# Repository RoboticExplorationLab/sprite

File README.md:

[hardware](https://github.com/maholli/sprite/tree/master/hardware): KiCad PCB files and bill of materials. Assembling a sprite? Check out [https://roboticexplorationlab.github.io/sprite/](https://roboticexplorationlab.github.io/sprite/) for an interactive BOM!

[firmware](https://github.com/maholli/sprite/tree/master/firmware): pre-built circuitpython bootloader.bin and firmware.uf2 (and the files to build it yourself)

[software](https://github.com/maholli/sprite/tree/master/software): circuitpython scripts and libraries working on the sprite

<br>
<br>
<br>

----

### 💡 Lots of applicable information also located on the [PyCubed.org quickstart page](https://www.notion.so/maholli/Hands-On-Quick-Start-d220f0ec88eb41c08ee855ff4f46d737).

## Demos

Put all the files located in [/software/](/software/) on to the sprite and start the serial console (as described above). After pressing <kbd>Ctrl</kbd>+<kbd>C</kbd> to halt the sprite, press any key to enter the REPL, then type

```
import NAMEOFFILE
```

and press enter to execute the example. For example, it we wanted to run blink.py, it would be...

```
import blink
```

1. blink.py - will blink the green LED. 
2. i2c_IMU.py - samples all available sensors on the IMU and prints the results
3. cursor.py - uses the X,Y data from the IMU accelerometer and moves the computer cursor accordingly
4. cpc_test.py - example transmit message for the CC1101 radio

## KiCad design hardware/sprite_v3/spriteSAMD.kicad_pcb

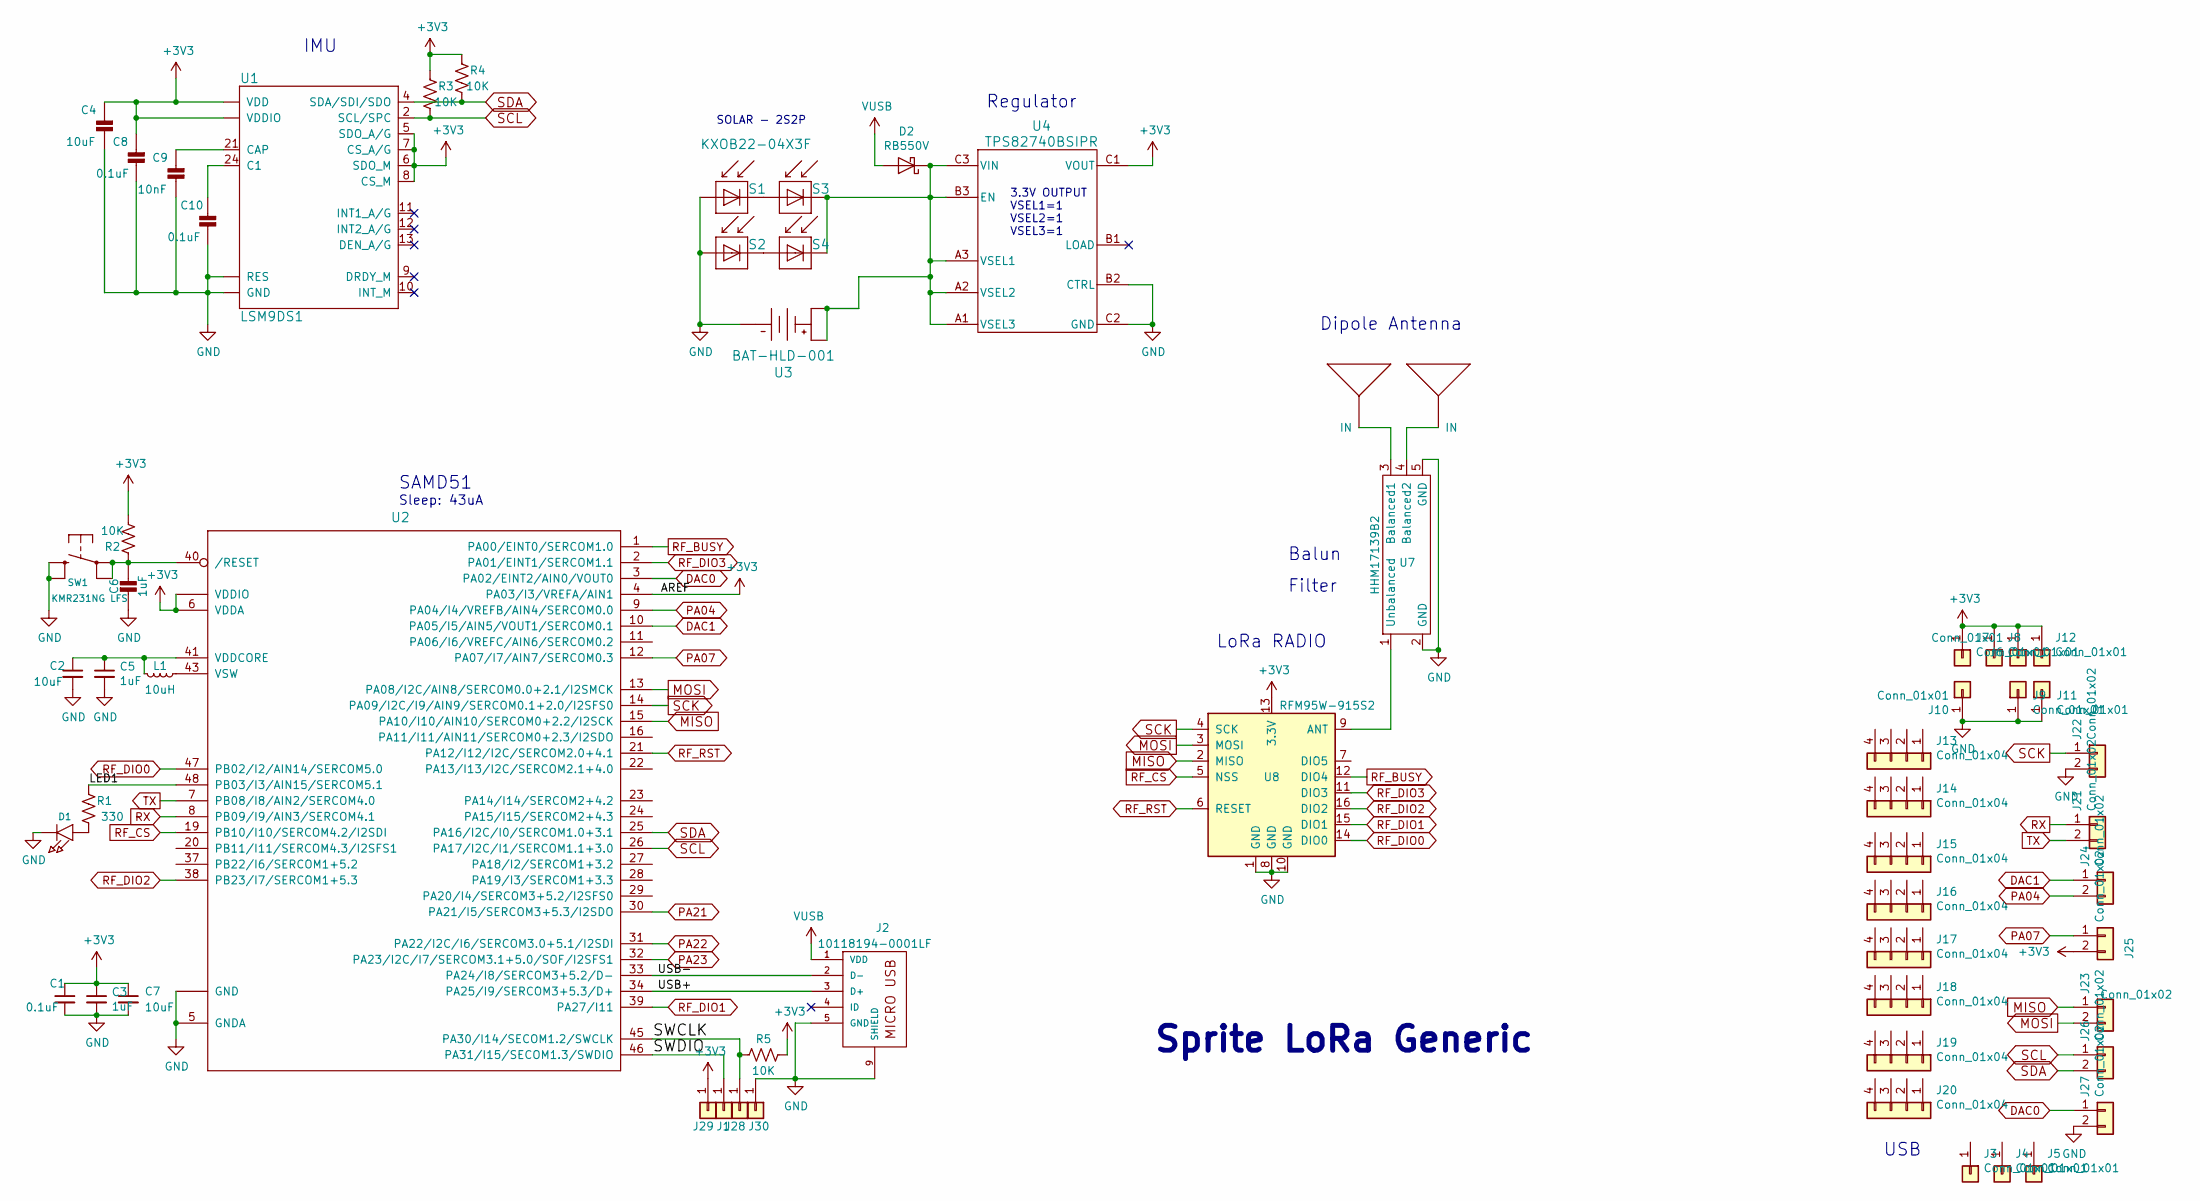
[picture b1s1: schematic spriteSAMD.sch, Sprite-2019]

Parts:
ANT1, ANT2: ANTENNA
C1, C8, C10: 0.1uF; C_0402_1005Metric
C2, C4, C7: 10uF; C_0402_1005Metric
C3, C5, C6: 1uF; C_0402_1005Metric
C9: 10nF; C_0402_1005Metric
D1: GREEN; LED_0603_1608Metric
D2: RB550V; D_SOD-323
J1, J28, J29, J30: Conn_01x01; castellated_small_1side
J2: 10118194-0001LF
J3, J4, J5, J6, J7, J8, J9, J10, J11, J12: Conn_01x01; PinHeader_CUSTOM2
J13, J14, J15, J16, J17, J18, J19, J20: Conn_01x04; PinHeader_CUSTOM
J21, J22, J23, J24, J25, J26, J27: Conn_01x02; PinHeader_CUSTOM3
L1: 10uH; L_0805_2012Metric
R1: 330; R_0402_1005Metric
R2, R3, R4, R5: 10K; R_0402_1005Metric
S1, S2, S3, S4: KXOB22-04X3F; KXOB22-12X1F
SW1: KMR231NG LFS; BTN_KMR2_4.6X2.8
U1: LSM9DS1; LGA24-8X4
U2: ATSAMD51G_TQFN48; QFN50P700X700X90-49N-D
U3: BAT-HLD-001
U4: TPS82740BSIPR; TPS82740ASIPR
U7: HHM17139B2; balun0603
U8: RFM95W-915S2; HOPERF_RFM9XW_SMD

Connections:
+3V3: C1.1, C3.1, C4.2, C7.1, C8.2, J6.1, J7.1, J8.1, J12.1, J25.2, J29.1, R2.2, R3.1, R4.1, R5.1, U1.1 (VDDIO), U1.3 (VDDIO), U1.5 (SDO_A/G), U1.6 (SDO_M), U1.7 (CS_A/G), U1.8 (CS_M), U1.22 (VDD), U1.23 (VDD), U2.4 (PA03/I3/VREFA/AIN1), U2.6 (VDDA), U2.17 (VDDIO), U2.36 (VDDIO), U2.44 (VDDIO), U4.C1 (VOUT), U8.13 (3.3V)
/LED1: R1.2, U2.48 (PB03/I3/AIN15/SERCOM5.1)
/SWCLK: J28.1, R5.2, U2.45 (PA30/I14/SECOM1.2/SWCLK)
/SWDIO: J1.1, U2.46 (PA31/I15/SECOM1.3/SWDIO)
/USB+: J2.3 (D+), U2.34 (PA25/I9/SERCOM3+5.3/D+)
/USB-: J2.2 (D-), U2.33 (PA24/I8/SERCOM3+5.2/D-)
DAC0: J27.1, U2.3 (PA02/EINT2/AIN0/VOUT0)
DAC1: J24.1, U2.10 (PA05/I5/AIN5/VOUT1/SERCOM0.1)
GND: C1.2, C2.2, C3.2, C4.1, C5.2, C6.1, C7.2, C8.1, C9.1, C10.1, D1.2, J2.5 (GND), J2.8, J2.9 (SHIELD), J9.1, J10.1, J11.1, J22.2, J27.2, J30.1, S1.2, S2.2, SW1.B (S), SW1.B' (S1), U1.14 (RES), U1.15 (RES), U1.16 (RES), U1.17 (RES), U1.18 (RES), U1.19 (GND), U1.20 (GND), U2.5 (GNDA), U2.18 (GND), U2.35 (GND), U2.42 (GND), U2.49, U3.2, U4.B2 (CTRL), U4.C2 (GND), U7.2 (GND), U7.5 (GND), U7.6 (NC), U8.1 (GND), U8.8 (GND), U8.10 (GND)
MISO: J23.1, U2.15 (PA10/I10/AIN10/SERCOM0+2.2/I2SCK), U8.2 (MISO)
MOSI: J23.2, U2.13 (PA08/I2C/AIN8/SERCOM0.0+2.1/I2SMCK), U8.3 (MOSI)
unnamed: ANT1.IN1, ANT1.IN2, ANT1.IN3, U7.3 (Balanced1)
unnamed: ANT2.IN1, ANT2.IN2, ANT2.IN3, U7.4 (Balanced2)
unnamed: C2.1, C5.1, L1.2, U2.41 (VDDCORE)
unnamed: C6.2, R2.1, SW1.A, SW1.A' (P1), U2.40 (/RESET)
unnamed: C9.2, U1.21 (CAP)
unnamed: C10.2, U1.24 (C1)
unnamed: D1.1, R1.1
unnamed: D2.1 (K), S3.1, S4.1, U3.1, U3.3, U4.A1 (VSEL3), U4.A2 (VSEL2), U4.A3 (VSEL1), U4.B3 (EN), U4.C3 (VIN)
unnamed: L1.1, U2.43 (VSW)
unnamed: S1.1, S3.2
unnamed: S2.1, S4.2
unnamed: U7.1 (Unbalanced), U8.9 (ANT)
PA04: J24.2, U2.9 (PA04/I4/VREFB/AIN4/SERCOM0.0)
PA07: J25.1, U2.12 (PA07/I7/AIN7/SERCOM0.3)
PA21: U2.30 (PA21/I5/SERCOM3+5.3/I2SDO)
PA22: U2.31 (PA22/I2C/I6/SERCOM3.0+5.1/I2SDI)
PA23: U2.32 (PA23/I2C/I7/SERCOM3.1+5.0/SOF/I2SFS1)
RF_BUSY: U2.1 (PA00/EINT0/SERCOM1.0), U8.12 (DIO4)
RF_CS: U2.19 (PB10/I10/SERCOM4.2/I2SDI), U8.5 (NSS)
RF_DIO0: U2.47 (PB02/I2/AIN14/SERCOM5.0), U8.14 (DIO0)
RF_DIO1: U2.39 (PA27/I11), U8.15 (DIO1)
RF_DIO2: U2.38 (PB23/I7/SERCOM1+5.3), U8.16 (DIO2)
RF_DIO3: U2.2 (PA01/EINT1/SERCOM1.1), U8.11 (DIO3)
RF_RST: U2.21 (PA12/I12/I2C/SERCOM2.0+4.1), U8.6 (RESET)
RX: J21.1, U2.8 (PB09/I9/AIN3/SERCOM4.1)
SCK: J22.1, U2.14 (PA09/I2C/I9/AIN9/SERCOM0.1+2.0/I2SFS0), U8.4 (SCK)
SCL: J26.1, R3.2, U1.2 (SCL/SPC), U2.26 (PA17/I2C/I1/SERCOM1.1+3.0)
SDA: J26.2, R4.2, U1.4 (SDA/SDI/SDO), U2.25 (PA16/I2C/I0/SERCOM1.0+3.1)
TX: J21.2, U2.7 (PB08/I8/AIN2/SERCOM4.0)
VUSB: D2.2 (A), J2.1 (VDD)

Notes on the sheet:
Regulator
USB
IMU
3.3V OUTPUT VSEL1=1 VSEL2=1 VSEL3=1
SOLAR - 2S2P
SAMD51
LoRa RADIO
Sleep: 43uA
Balun
Filter
Dipole Antenna
Sprite LoRa Generic

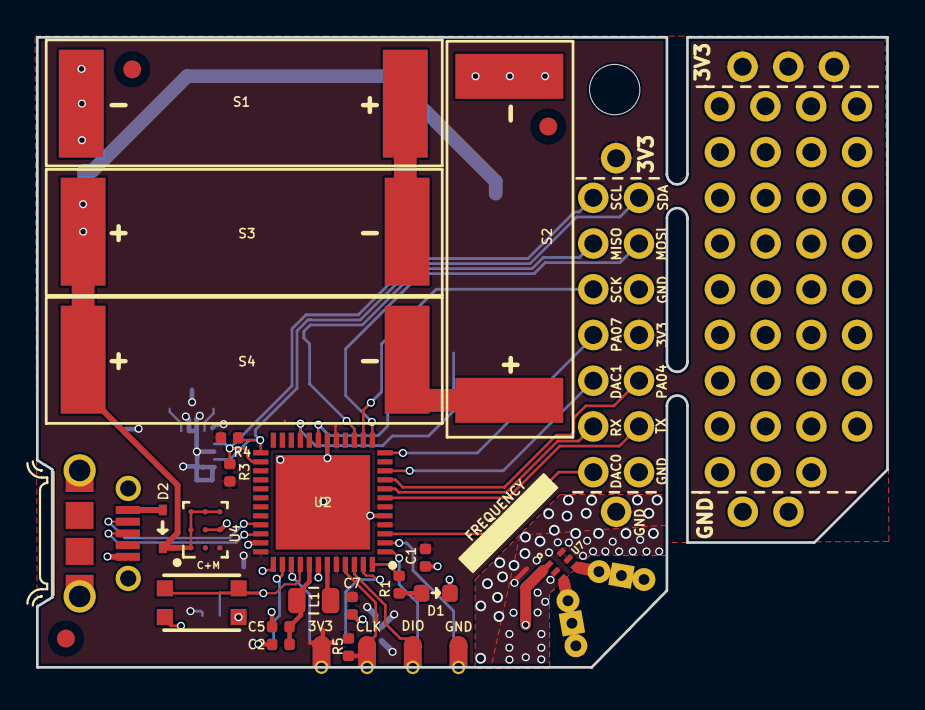
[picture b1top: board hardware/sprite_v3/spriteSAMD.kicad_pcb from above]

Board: 2 copper layers, 47.2 x 35.0 mm, 62 parts (0 on the bottom side), 38 nets.

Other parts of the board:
@HOLE0: (no value)

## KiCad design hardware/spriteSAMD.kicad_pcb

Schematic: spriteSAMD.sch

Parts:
ANT-N1: ANTENNA
ANT-P1: ANTENNA
C1, C30, C34: 10uF; C_0402_1005Metric
C2, C3, C4, C6, C8, C9, C10, C32: 0.1uF; C_0402_1005Metric
C5, C18, C20: 10nF; C_0402_1005Metric
C7, C29, C31, C33: 1uF; C_0402_1005Metric
C16, C17, C19: 220pF; C_0402_1005Metric
C21, C22: 100nF; C_0402_1005Metric
C25: 27pF; C_0402_1005Metric
D1: MBR120; D_SOD-123
D3: GREEN LED; LED_0603_1608Metric
J1: 10118194-0001LF
J2, J4, J5, J6, J7, J8, J9, J10, J11, J12: Conn_01x01; PinHeader_CUSTOM2
J3: Conn_01x04; PinHeader_1x04_P2.54mm_Vertical
J13, J14, J15, J16, J17, J18, J19, J20: Conn_01x04; PinHeader_CUSTOM
J21, J22, J23, J24, J25, J26, J27: Conn_01x02; PinHeader_CUSTOM3
JP1: SolderJumper_3_Bridged12; Jumper3_Small
L1: 10uH; L_0805_2012Metric
R6: 330; R_0402_1005Metric
R7, R8, R9, R13: 10K; R_0402_1005Metric
R11: 56K; R_0402_1005Metric
S1, S2, S3, S5: KXOB22-04X3F; KXOB22-12X1F
SW2: KMR231NG LFS; BTN_KMR2_4.6X2.8
U1: BAT-HLD-001
U2: CC1101RGPR; CC1101_RGP_20; MPN CC1101RGPR; Digi-Key_PN 296-35718-1-ND
U3: LSM9DS1; LGA24-8X4
U4: TPS82740ASIP; TPS82740ASIPR
U6: ATSAMD51G_TQFN48; QFN50P700X700X90-49N-D
U7: OVM9724; OVM9724b
U8, U9: DS90LV012ATMFX_NOPB; DS90
X1: 26.000; TXCO_2.5x2

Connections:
+2V1: C1.2, C2.1, C3.1, C4.2, C16.2, C17.1, C18.1, C19.1, C20.1, C22.2, C31.2, C32.1, C33.1, C34.1, J3.4, J6.1, J9.1, J11.1, R7.1, R8.1, R9.2, R13.1, U2.4, U2.9, U2.11, U2.14, U2.15, U2.18, U3.1 (VDDIO), U3.3 (VDDIO), U3.5 (SDO_A/G), U3.6 (SDO_M), U3.7 (CS_A/G), U3.8 (CS_M), U3.22 (VDD), U3.23 (VDD), U4.C1 (VOUT), U6.6 (VDDA), U6.17 (VDDIO), U6.36 (VDDIO), U6.44 (VDDIO), U7.C2 (DOVDD), U7.C7 (DVDD), U7.D6 (DOVDD), U8.1 (Vdd), U9.1 (Vdd), X1.4
/AREF: C31.1, U6.4 (PA03/I3/VREFA/AIN1)
/AVDD: C8.1, U7.A2 (AVDD)
/LED1: R6.2, U6.48 (PB03/I3/AIN15/SERCOM5.1)
/SWCLK: J3.2, R13.2, U6.45 (PA30/I14/SECOM1.2/SWCLK)
/SWDIO: J3.3, U6.46 (PA31/I15/SECOM1.3/SWDIO)
/USB+: J1.3 (D+), U6.34 (PA25/I9/SERCOM3+5.3/D+)
/USB-: J1.2 (D-), U6.33 (PA24/I8/SERCOM3+5.2/D-)
/VREF1: C9.1, U7.D2 (VREF1)
/VREF2: C10.1, U7.D3 (VREF2)
DAC0: J27.1, U6.3 (PA02/EINT2/AIN0/VOUT0)
FSYNC: U6.22 (PA13/I13/I2C/SERCOM2.1+4.0), U6.24 (PA15/I15/SERCOM2+4.3), U7.C5 (GPIO0/FSIN)
MC: U6.28 (PA19/I3/SERCOM1+3.3), U9.5 (TTLout)
MD: U6.27 (PA18/I2/SERCOM1+3.2), U8.5 (TTLout)
MISO: J21.2, U2.2, U6.9 (PA04/I4/VREFB/AIN4/SERCOM0.0)
MOSI: J24.2, U2.20, U6.12 (PA07/I7/AIN7/SERCOM0.3)
unnamed: ANT-N1.IN1, ANT-N1.IN2, ANT-N1.IN3, U2.13
unnamed: ANT-P1.IN1, ANT-P1.IN2, ANT-P1.IN3, U2.12
unnamed: C5.2, U3.21 (CAP)
unnamed: C6.2, U3.24 (C1)
unnamed: C21.1, U2.5
unnamed: C25.1, U2.8
unnamed: C25.2, X1.3
unnamed: C29.2, R9.1, SW2.A, SW2.A' (P1), U6.40 (/RESET)
unnamed: C7.2, C30.2, L1.2, U6.41 (VDDCORE)
unnamed: D1.1, JP1.3, S2.1, S3.1, U1.1, U1.3, U4.A2 (VSEL2), U4.A3 (VSEL1), U4.B3 (EN), U4.C3 (VIN)
unnamed: D3.1, R6.1
unnamed: JP1.2, U4.A1 (VSEL3)
unnamed: L1.1, U6.43 (VSW)
unnamed: R11.1, U2.17
unnamed: S1.1, S2.2
unnamed: S3.2, S5.1
unnamed: U7.A5 (MDP), U8.4 (IN-)
unnamed: U7.B5 (MDN), U8.3 (IN+)
unnamed: U7.B6 (MCN), U9.4 (IN-)
unnamed: U7.C6 (MCP), U9.3 (IN+)
PA06: J24.1, U6.11 (PA06/I6/VREFC/AIN6/SERCOM0.2)
PA08: J22.1, U6.13 (PA08/I2C/AIN8/SERCOM0.0+2.1/I2SMCK)
PA09: J23.2, U6.14 (PA09/I2C/I9/AIN9/SERCOM0.1+2.0/I2SFS0)
PA10: J23.1, U6.15 (PA10/I10/AIN10/SERCOM0+2.2/I2SCK)
PA21: U6.30 (PA21/I5/SERCOM3+5.3/I2SDO)
PA22: U6.31 (PA22/I2C/I6/SERCOM3.0+5.1/I2SDI)
PA23: U6.32 (PA23/I2C/I7/SERCOM3.1+5.0/SOF/I2SFS1)
PB02: U6.47 (PB02/I2/AIN14/SERCOM5.0)
PWDWN: U6.20 (PB11/I11/SERCOM4.3/I2SFS1), U7.B1 (PWDNB)
RX: J25.1, U6.7 (PB08/I8/AIN2/SERCOM4.0)
SCK: J21.1, U2.1, U6.10 (PA05/I5/AIN5/VOUT1/SERCOM0.1)
SCL: J26.2, R7.2, U3.2 (SCL/SPC), U6.26 (PA17/I2C/I1/SERCOM1.1+3.0), U7.A4 (SCL)
SDA: J26.1, R8.2, U3.4 (SDA/SDI/SDO), U6.25 (PA16/I2C/I0/SERCOM1.0+3.1), U7.A6 (SDA)
SHDWN: U6.19 (PB10/I10/SERCOM4.2/I2SDI), U7.B2 (~SHUTDOWN)
TST: U6.16 (PA11/I11/AIN11/SERCOM0+2.3/I2SDO), U7.B3 (TM)
TX: J25.2, U6.8 (PB09/I9/AIN3/SERCOM4.1)
VCLK: U6.23 (PA14/I14/SERCOM2+4.2), U7.C3 (~VCLK)
VUSB: D1.2, J1.1 (VDD)
WAKE: U2.6, U6.2 (PA01/EINT1/SERCOM1.1)
radioCS: U2.7, U6.1 (PA00/EINT0/SERCOM1.0)

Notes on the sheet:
REGULATOR
PCCDEN1
PCCDEN2
PCCD0
PCCD1
PCCD2
PCCD3
PCCD4
PCCD5
PCCD6
PCCD7
PCCLK
USB
IMU
100ohm diff pair
I2C=0x20
2.1V OUTPUT VSEL1=1 VSEL2=1 VSEL3=0
SOLAR - 2S2P
Sprite - 2019
SAMD51

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
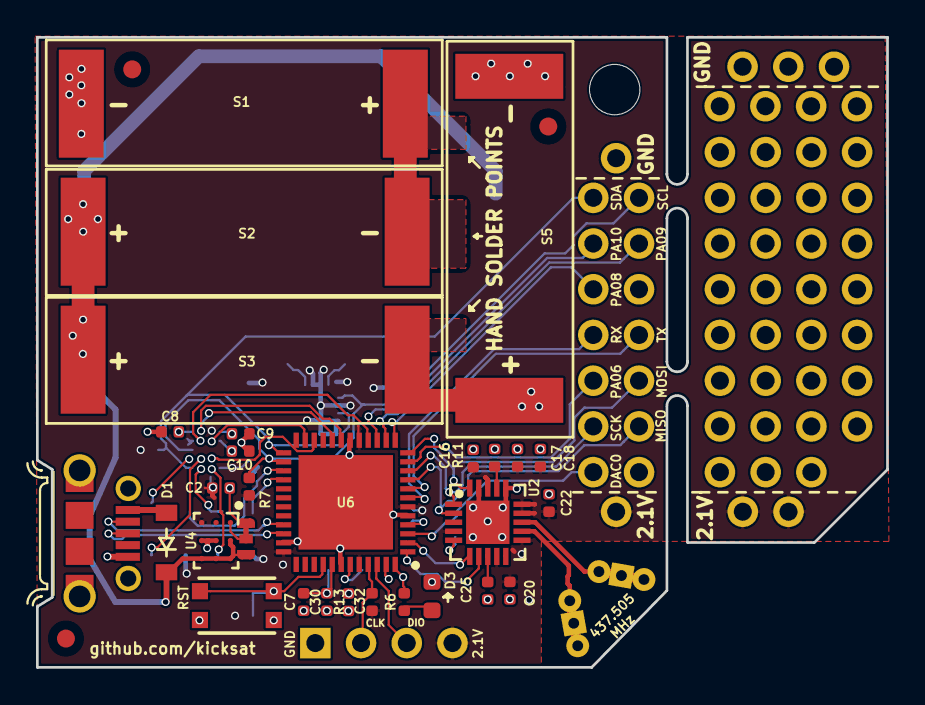
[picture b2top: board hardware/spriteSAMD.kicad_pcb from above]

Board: 2 copper layers, 47.2 x 35.0 mm, 78 parts (0 on the bottom side), 53 nets.

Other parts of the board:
@HOLE0: (no value)

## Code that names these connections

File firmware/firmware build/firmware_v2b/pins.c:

#include "shared-bindings/board/__init__.h"

#include "supervisor/shared/board_busses.h"

STATIC const mp_rom_map_elem_t board_global_dict_table[] = {
    { MP_ROM_QSTR(MP_QSTR_SCK),     MP_ROM_PTR(&pin_PA05)  },
    { MP_ROM_QSTR(MP_QSTR_MOSI),    MP_ROM_PTR(&pin_PA07)  },
    { MP_ROM_QSTR(MP_QSTR_MISO),    MP_ROM_PTR(&pin_PA04)  },

    { MP_ROM_QSTR(MP_QSTR_radioCS), MP_ROM_PTR(&pin_PA00)  },
    { MP_ROM_QSTR(MP_QSTR_WAKE),    MP_ROM_PTR(&pin_PA01)  },
	{ MP_ROM_QSTR(MP_QSTR_SHDWN),   MP_ROM_PTR(&pin_PB10)  },
    { MP_ROM_QSTR(MP_QSTR_PWDWN),   MP_ROM_PTR(&pin_PB11)  },
    { MP_ROM_QSTR(MP_QSTR_TST),     MP_ROM_PTR(&pin_PA11)  },
    { MP_ROM_QSTR(MP_QSTR_FSYNC),   MP_ROM_PTR(&pin_PA13)  },
	{ MP_ROM_QSTR(MP_QSTR_VCLK),    MP_ROM_PTR(&pin_PA14)  },
    { MP_ROM_QSTR(MP_QSTR_FSYNC),   MP_ROM_PTR(&pin_PA15)  },
    { MP_ROM_QSTR(MP_QSTR_MD),   	MP_ROM_PTR(&pin_PA18)  },
    { MP_ROM_QSTR(MP_QSTR_MC),   	MP_ROM_PTR(&pin_PA19)  },

    { MP_ROM_QSTR(MP_QSTR_PA08),   	MP_ROM_PTR(&pin_PA08)  },
    { MP_ROM_QSTR(MP_QSTR_PA10),   	MP_ROM_PTR(&pin_PA10)  },
    { MP_ROM_QSTR(MP_QSTR_PA09),   	MP_ROM_PTR(&pin_PA09)  },
    { MP_ROM_QSTR(MP_QSTR_PA06),   	MP_ROM_PTR(&pin_PA06)  },
    { MP_ROM_QSTR(MP_QSTR_DAC0),   	MP_ROM_PTR(&pin_PA02)  },
   
    { MP_ROM_QSTR(MP_QSTR_TX),      MP_ROM_PTR(&pin_PB09)  },
    { MP_ROM_QSTR(MP_QSTR_RX),      MP_ROM_PTR(&pin_PB08)  },
    { MP_ROM_QSTR(MP_QSTR_SDA),     MP_ROM_PTR(&pin_PA16)  },
    { MP_ROM_QSTR(MP_QSTR_SCL),     MP_ROM_PTR(&pin_PA17)  },


    { MP_ROM_QSTR(MP_QSTR_LED),     MP_ROM_PTR(&pin_PB03)  },
    
    { MP_ROM_QSTR(MP_QSTR_UART),    MP_ROM_PTR(&board_uart_obj) },
    { MP_ROM_QSTR(MP_QSTR_I2C),     MP_ROM_PTR(&board_i2c_obj)  },
    { MP_ROM_QSTR(MP_QSTR_SPI),     MP_ROM_PTR(&board_spi_obj)  },
};
MP_DEFINE_CONST_DICT(board_module_globals, board_global_dict_table);

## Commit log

2019-02-07 initial commit of v2a will need to update hardware to v2b
2019-02-07 adding details on how to run software examples
2019-02-07 adding interactive BOM
2019-02-07 fixing image path
2019-02-15 updating to v2b (TXCO added)
2019-02-15 Via drills changed 0.25 to 0.3 mm
2019-02-16 silly fixes for fab house
2019-03-03 updating firmware for v2b
2019-03-03 new board image
2019-03-04 adding quick glamor shot
2019-10-18 finally adding modular radio version + repo cleanup

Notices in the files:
parts and their libraries:
Copyright 2016 Accelerated Designs. All rights reserved.
